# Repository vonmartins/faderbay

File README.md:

# FADERBAY

Current Status: Firmware not finnished.

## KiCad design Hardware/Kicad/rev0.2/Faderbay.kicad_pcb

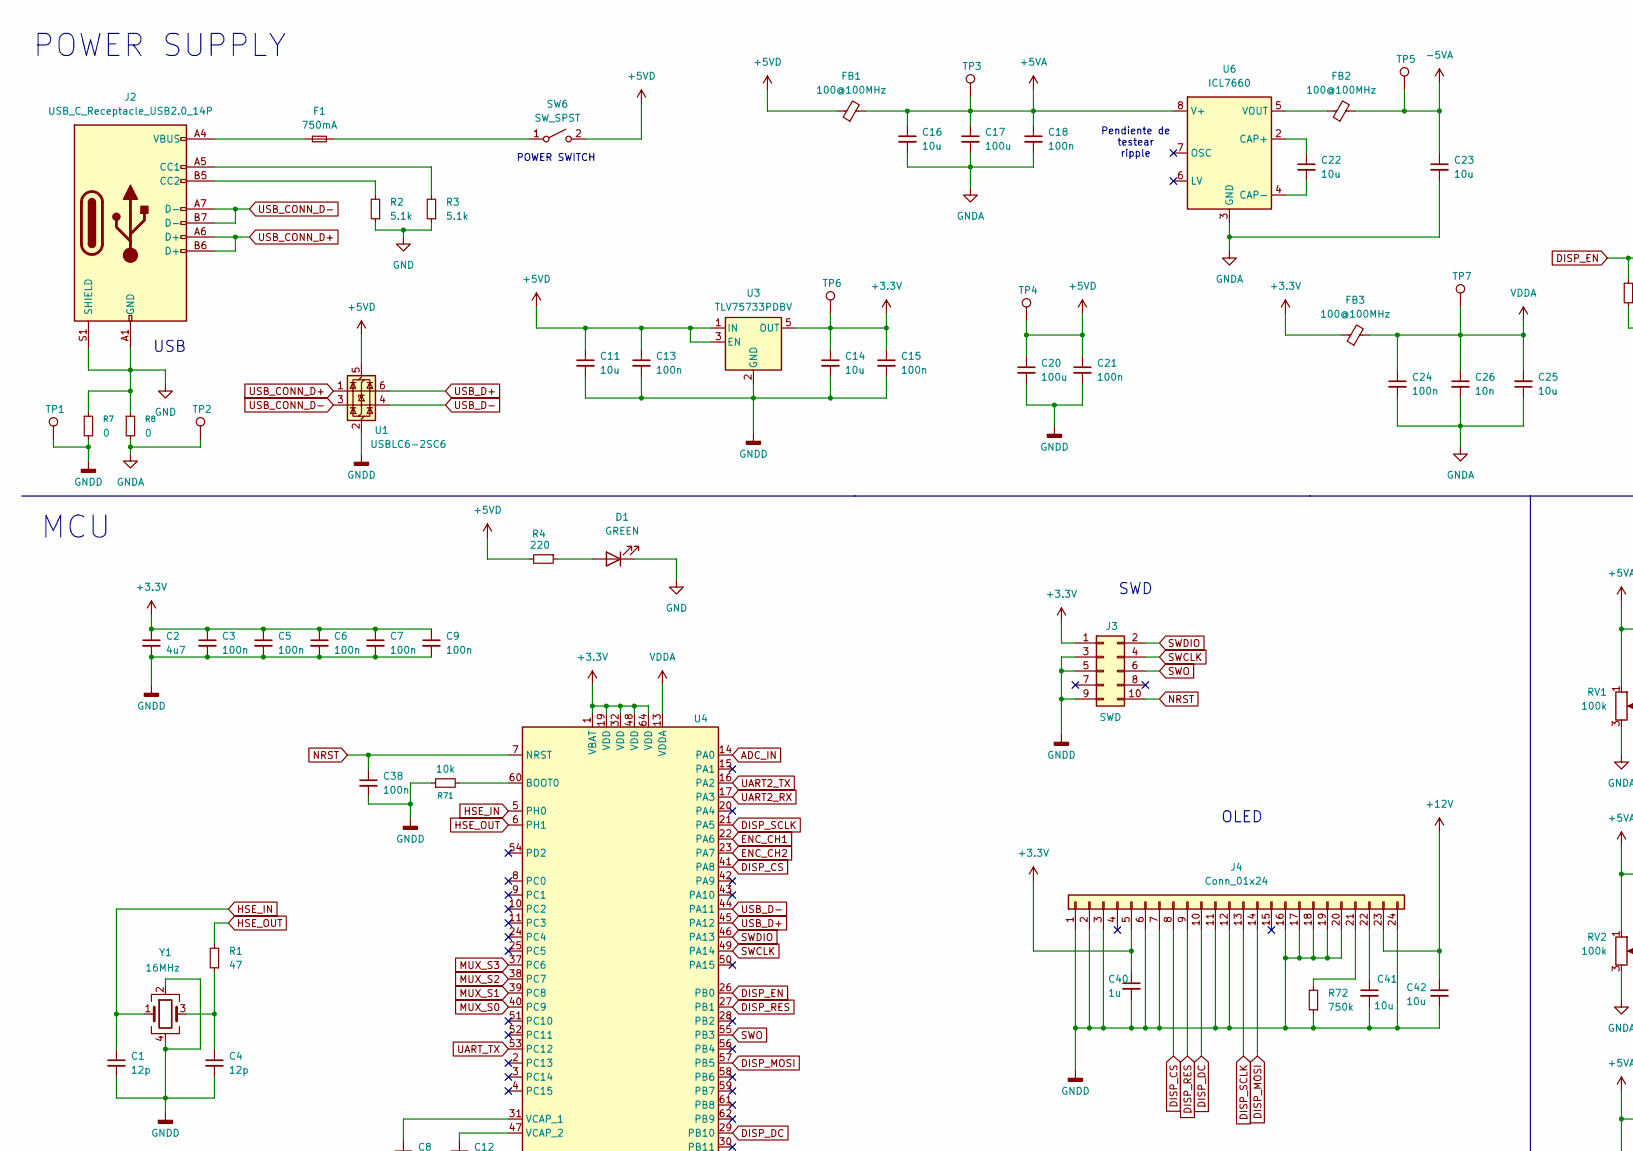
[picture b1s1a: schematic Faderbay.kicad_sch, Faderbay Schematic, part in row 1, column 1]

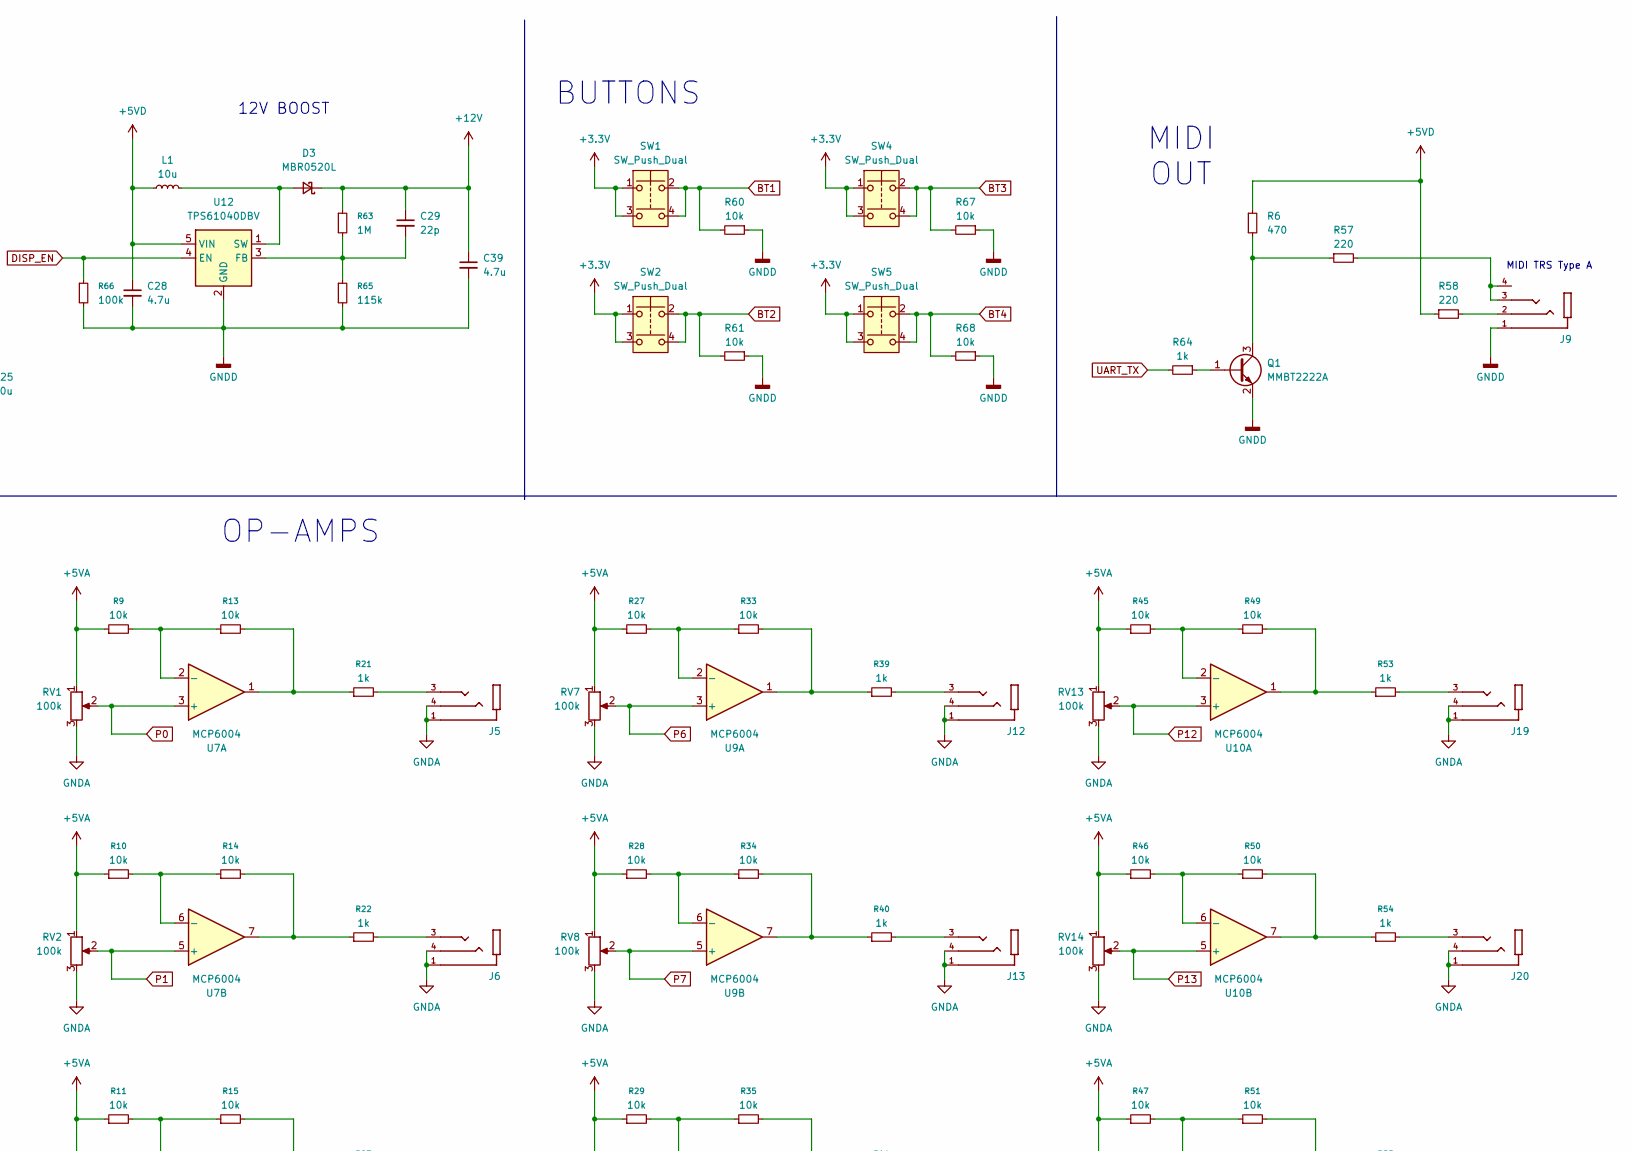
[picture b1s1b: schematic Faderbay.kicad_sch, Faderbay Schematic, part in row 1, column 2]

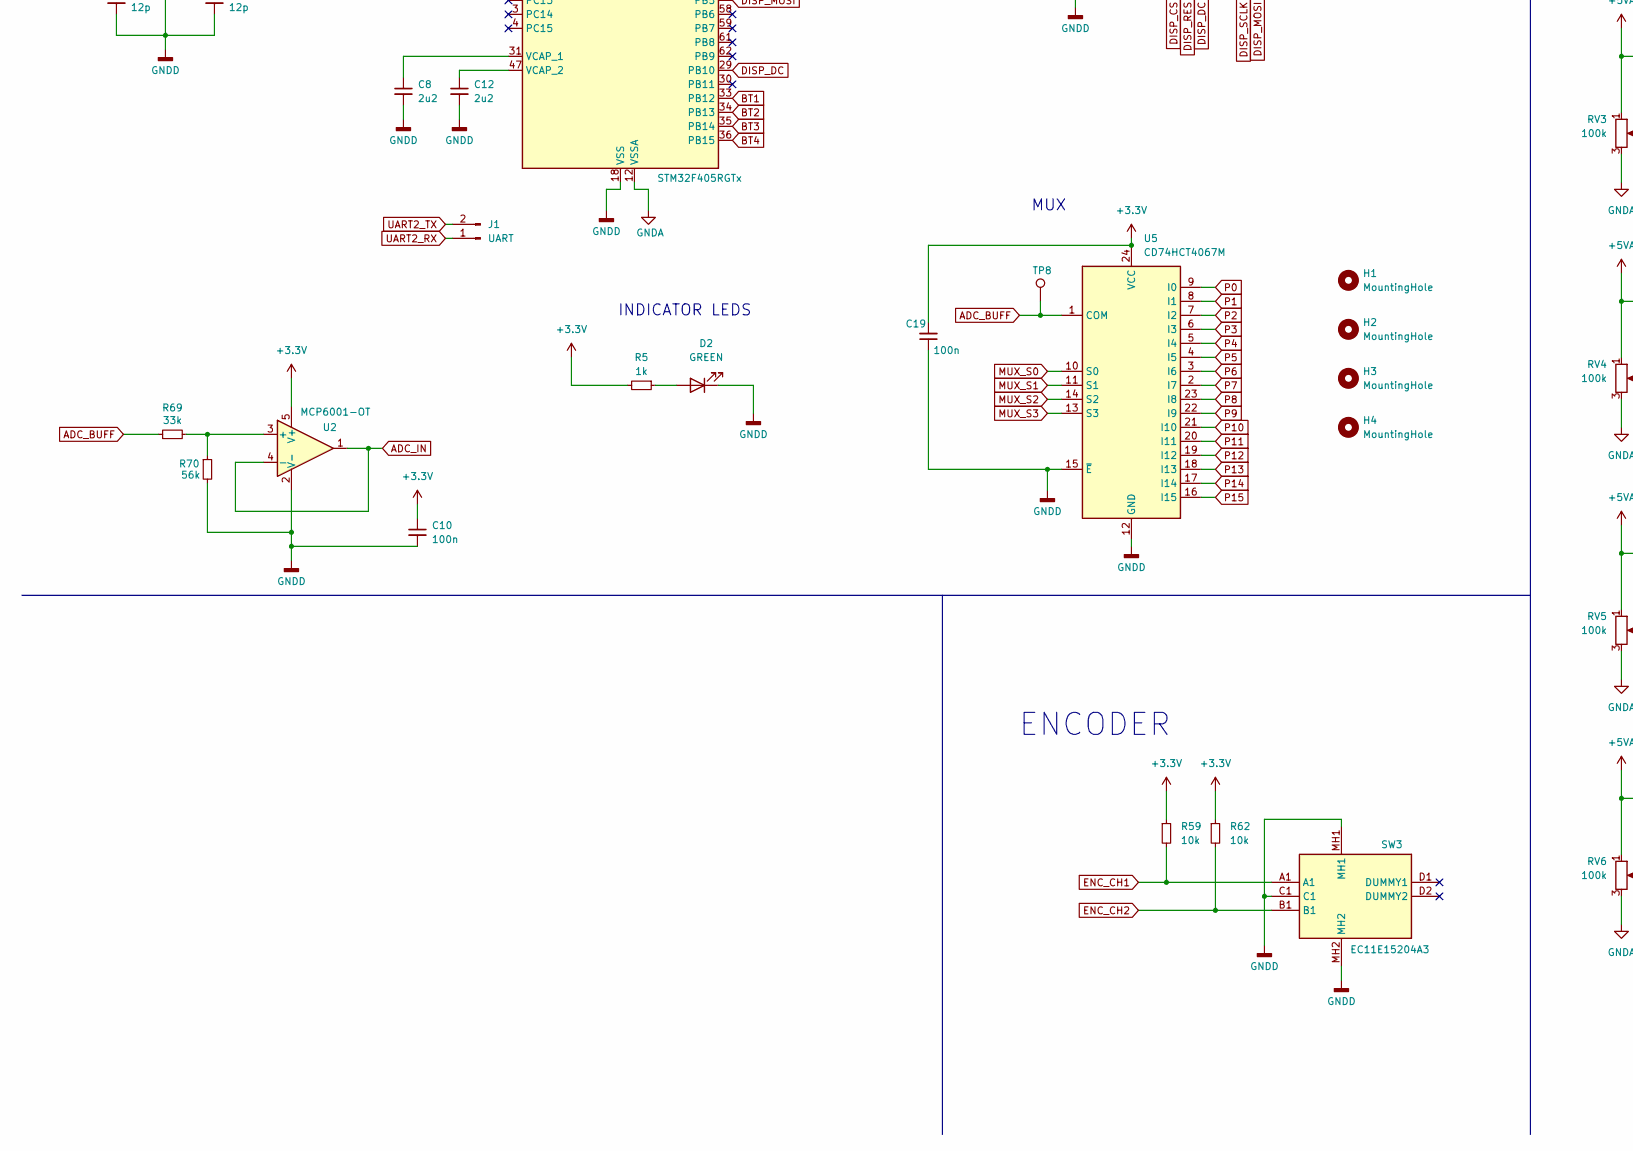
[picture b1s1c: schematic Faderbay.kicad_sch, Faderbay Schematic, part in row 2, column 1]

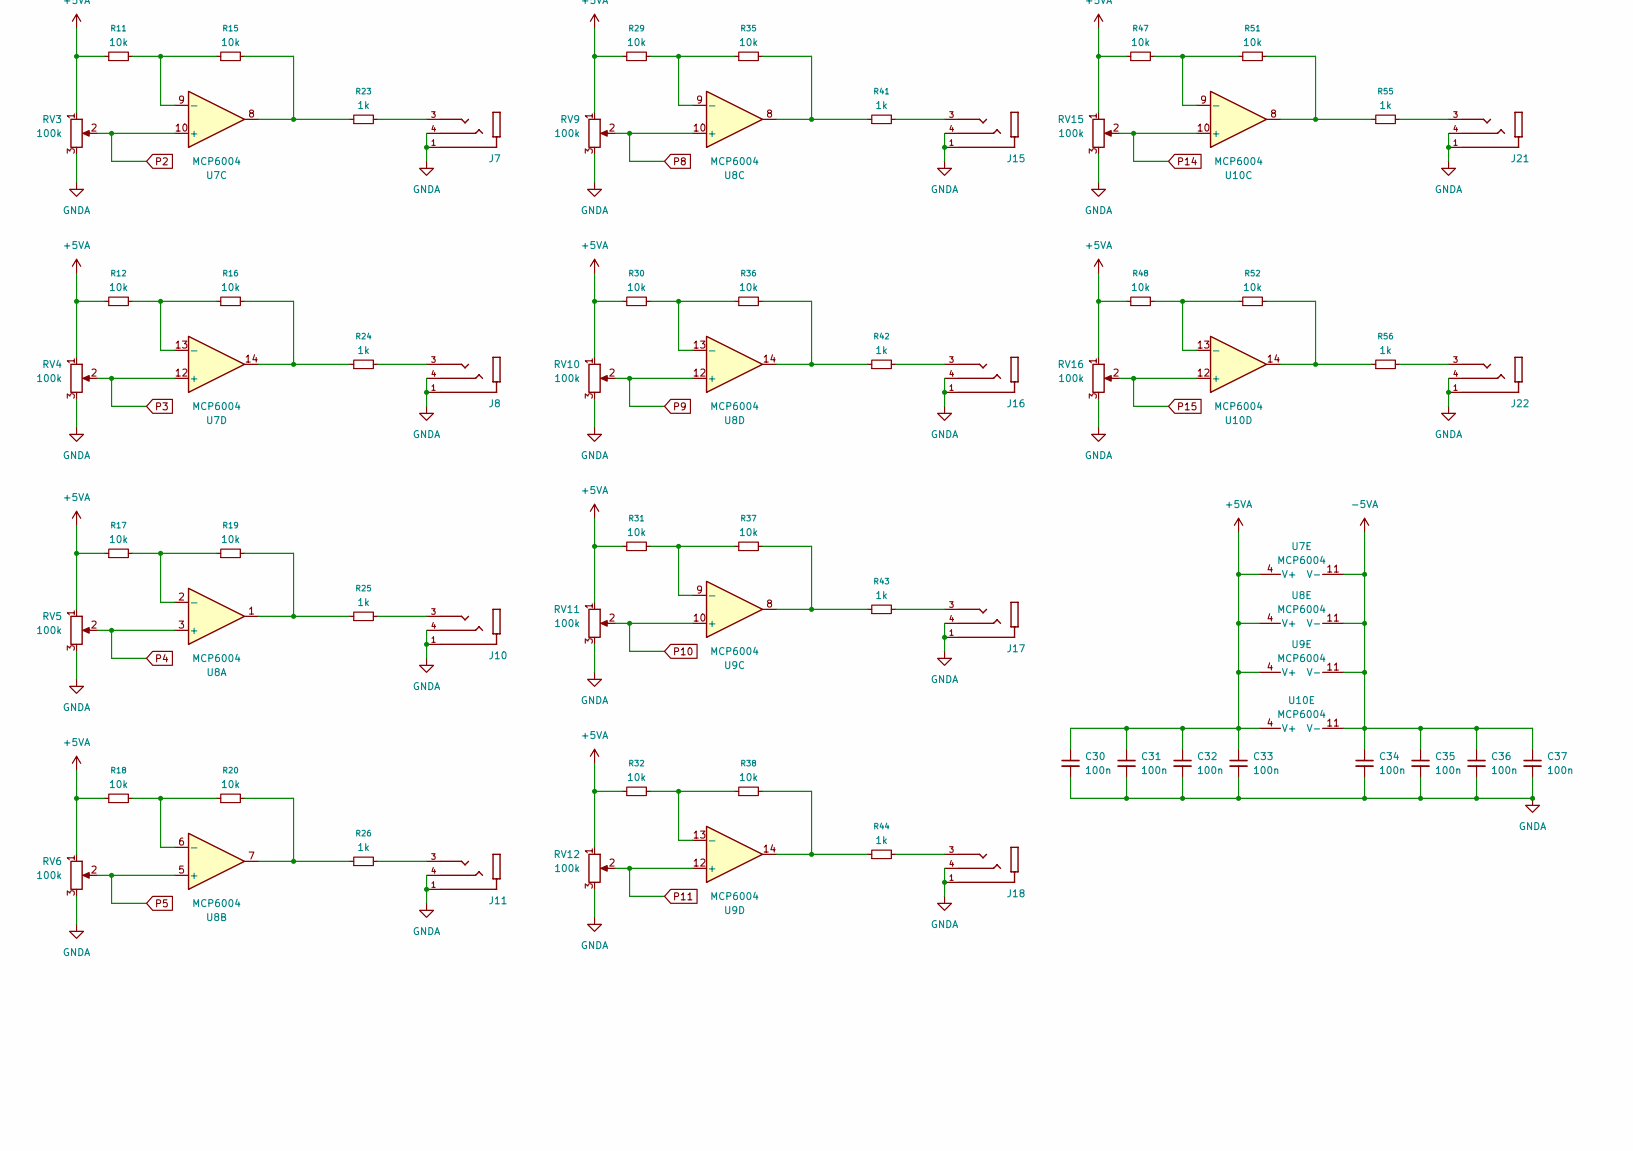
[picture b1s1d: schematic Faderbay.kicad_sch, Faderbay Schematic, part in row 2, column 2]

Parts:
C1, C4: 12p; C_0603_1608Metric; LCSC Part # C38523
C2: 4u7; C_0805_2012Metric; LCSC Part # C19666
C3, C5, C6, C7, C9, C13, C19: 100n; C_0402_1005Metric; LCSC Part # C1525
C8, C12: 2u2; C_0805_2012Metric; LCSC Part # C377773
C10, C15, C18, C30, C31, C32, C33, C34, C35, C36, C37, C38: 100n; C_0402_1005Metric
C11, C14, C16, C23: 10u; C_0805_2012Metric
C17: 100u; C_1206_3216Metric; LCSC Part # C12891
C20: 100u; C_1206_3216Metric
C21, C24: 100n; C_0402_1005Metric; LCSC Part # C52923
C22: 10u; C_1206_3216Metric
C25: 10u; C_0603_1608Metric; LCSC Part # C52923
C26: 10n; C_0402_1005Metric; LCSC Part # C52923
C28, C39: 4.7u; C_0805_2012Metric
C29: 22p; C_0402_1005Metric
C40: 1u; C_0603_1608Metric
C41, C42: 10u; C_0603_1608Metric
D1: GREEN; WP934EWGD
D2: GREEN; LED_0805_2012Metric; LCSC Part # C2297
D3: MBR0520L; D_0805_2012Metric
F1: 750mA; Fuse_1206_3216Metric
FB1, FB2, FB3: 100@100MHz; L_0805_2012Metric
H1, H2, H3, H4: MountingHole; MountingHole_3.2mm_M3
J1: UART; PinHeader_1x02_P2.54mm_Vertical
J2: USB_C_Receptacle_USB2.0_14P; USB_C_Receptacle_HRO_TYPE-C-31-M-12; LCSC Part # C5119948
J3: SWD; PinSocket_2x05_P1.27mm_Vertical_SMD; LCSC Part # C350283
J4: Conn_01x24; Jushuo_AFC07-S24FCA-00_1x24-1MP_P0.50_Horizontal
J5, J6, J7, J8, J10, J11, J12, J13, J15, J16, J17, J18, J19, J20, J21, J22: WQP729JH-R; LCSC Part # C18594
J9: WQP729JH-B; LCSC Part # C18594
L1: 10u; L_Sunlord_SWPA4030S
Q1: MMBT2222A; SOT-23; LCSC Part # C8512
R1: 47; R_0603_1608Metric; LCSC Part # C23182
R2, R3: 5.1k; R_0402_1005Metric; LCSC Part # C23186
R4: 220; R_0603_1608Metric; LCSC Part # C23193
R5: 1k; R_0603_1608Metric; LCSC Part # C17556
R6: 470; R_0603_1608Metric
R7: 0; R_0603_1608Metric; LCSC Part # C25803
R8: 0; R_0603_1608Metric; LCSC Part # C22793
R9, R10, R11, R12, R13, R14, R15, R16, R17, R18, R19, R20, R27, R28, R29, R30, R31, R32, R33, R34, R35, R36, R37, R38, R45, R46, R47, R48, R49, R50, R51, R52: 10k; R_0402_1005Metric
R21, R22, R39, R40, R53, R54: 1k; R_0603_1608Metric; LCSC Part # C4184
R23, R24, R25, R26, R41, R42, R43, R44, R55, R56: 1k; R_0603_1608Metric; LCSC Part # C21190
R57, R58: 220; R_0805_2012Metric; LCSC Part # C17556
R59, R60, R61, R62, R67, R68: 10k; R_0402_1005Metric; LCSC Part # C25531
R63: 1M; R_0402_1005Metric
R64: 1k; R_0402_1005Metric; LCSC Part # C25531
R65: 115k; R_0402_1005Metric
R66: 100k; R_0603_1608Metric
R69: 33k; R_0402_1005Metric
R70: 56k; R_0402_1005Metric
R71: 10k; C_0402_1005Metric
R72: 750k; R_0603_1608Metric
RV1, RV2, RV3, RV4, RV5, RV6, RV7, RV8, RV9, RV10, RV11, RV12, RV13, RV14, RV15, RV16: 100k; Potentiometer_Bourns_PTA6043_Single_Slide
SW1, SW2, SW4, SW5: SW_Push_Dual; 430182070816; LCSC Part # C318884
SW3: EC11E15204A3; Mouser Part Number 688-EC11E15204A3
SW6: SW_SPST; RA1H1C112R
TP1, TP2, TP3, TP4, TP5, TP6, TP7, TP8: TestPoint; TestPoint_Loop_D2.50mm_Drill1.0mm
U1: USBLC6-2SC6; SOT-23-6; LCSC Part # C7519
U2: MCP6001-OT; SOT-23-5
U3: TLV75733PDBV; SOT-23-5
U4: STM32F405RGTx; LQFP-64_10x10mm_P0.5mm; LCSC Part # C15742
U5: CD74HCT4067M; SOIC-24W_7.5x15.4mm_P1.27mm; LCSC Part # C496123
U6: ICL7660; SOIC-8_3.9x4.9mm_P1.27mm
U7, U8, U9, U10: MCP6004; TSSOP-14_4.4x5mm_P0.65mm
U12: TPS61040DBV; SOT-23-5
Y1: 16MHz; Crystal_SMD_3225-4Pin_3.2x2.5mm; LCSC Part # C13738

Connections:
+3.3V: C2.1, C3.1, C5.1, C6.1, C7.1, C9.1, C10.1, C14.1, C15.1, C19.2, C40.1, FB3.1, J3.1, J4.5, R5.2, R59.1, R62.1, SW1.1, SW1.3, SW2.1, SW2.3, SW4.1, SW4.3, SW5.1, SW5.3, TP6.1 (1_1), U2.5 (V+), U3.5 (OUT), U4.1 (VBAT), U4.19 (VDD), U4.32 (VDD), U4.48 (VDD), U4.64 (VDD), U5.24 (VCC)
+5VA: C16.1, C17.1, C18.1, C30.1, C31.1, C32.1, C33.1, FB1.2, R9.1, R10.1, R11.1, R12.1, R17.1, R18.1, R27.1, R28.1, R29.1, R30.1, R31.1, R32.1, R45.1, R46.1, R47.1, R48.1, RV1.1, RV2.1, RV3.1, RV4.1, RV5.1, RV6.1, RV7.1, RV8.1, RV9.1, RV10.1, RV11.1, RV12.1, RV13.1, RV14.1, RV15.1, RV16.1, TP3.1 (1_1), U6.8 (V+), U7.4 (V+), U8.4 (V+), U9.4 (V+), U10.4 (V+)
+12V: C29.1, C39.1, C42.1, D3.1 (K), J4.23, R63.1
-5VA: C23.1, C34.1, C35.1, C36.1, C37.1, FB2.2, TP5.1 (1_1), U7.11 (V-), U8.11 (V-), U9.11 (V-), U10.11 (V-)
ADC_BUFF: R69.1, TP8.1 (1_1), U5.1 (COM)
ADC_IN: U2.1, U2.4 (-), U4.14 (PA0)
BT1: R60.2, SW1.2, SW1.4, U4.33 (PB12)
BT2: R61.2, SW2.2, SW2.4, U4.34 (PB13)
BT3: R67.2, SW4.2, SW4.4, U4.35 (PB14)
BT4: R68.2, SW5.2, SW5.4, U4.36 (PB15)
DISP_CS: J4.8, U4.41 (PA8)
DISP_DC: J4.10, U4.29 (PB10)
DISP_EN: R66.1, U4.26 (PB0), U12.4 (EN)
DISP_MOSI: J4.14, U4.57 (PB5)
DISP_RES: J4.9, U4.27 (PB1)
DISP_SCLK: J4.13, U4.21 (PA5)
ENC_CH1: R59.2, SW3.A1, U4.22 (PA6)
ENC_CH2: R62.2, SW3.B1, U4.23 (PA7)
GND: D1.1 (K), J2.A1 (GND), J2.A12 (GND), J2.B1 (GND), J2.B12 (GND), J2.S1 (SHIELD), R2.1, R3.1, R7.1, R8.1
GNDA: C16.2, C17.2, C18.2, C23.2, C24.2, C25.1, C26.2, C30.2, C31.2, C32.2, C33.2, C34.2, C35.2, C36.2, C37.2, J5.1, J5.4, J6.1, J6.4, J7.1, J7.4, J8.1, J8.4, J10.1, J10.4, J11.1, J11.4, J12.1, J12.4, J13.1, J13.4, J15.1, J15.4, J16.1, J16.4, J17.1, J17.4, J18.1, J18.4, J19.1, J19.4, J20.1, J20.4, J21.1, J21.4, J22.1, J22.4, R8.2, RV1.3, RV2.3, RV3.3, RV4.3, RV5.3, RV6.3, RV7.3, RV8.3, RV9.3, RV10.3, RV11.3, RV12.3, RV13.3, RV14.3, RV15.3, RV16.3, TP2.1 (1_1), U4.12 (VSSA), U6.3 (GND)
HSE_IN: C1.1, U4.5 (PH0), Y1.1
HSE_OUT: R1.2, U4.6 (PH1)
MUX_S0: U4.40 (PC9), U5.10 (S0)
MUX_S1: U4.39 (PC8), U5.11 (S1)
MUX_S2: U4.38 (PC7), U5.14 (S2)
MUX_S3: U4.37 (PC6), U5.13 (S3)
NRST: C38.1, J3.10, U4.7 (NRST)
unnamed: C4.1, R1.1, Y1.3
unnamed: D1.2 (A), R4.1
unnamed: D2.2 (A), R5.1
unnamed: D3.2 (A), L1.2, U12.1 (SW)
unnamed: F1.1, J2.A4 (VBUS), J2.A9 (VBUS), J2.B4 (VBUS), J2.B9 (VBUS)
unnamed: J2.A5 (CC1), R3.2
unnamed: J2.B5 (CC2), R2.2
unnamed: J4.21, R72.2
unnamed: C41.1, J4.22
unnamed: J5.3, R21.2
unnamed: J6.3, R22.2
unnamed: J7.3, R23.2
unnamed: J8.3, R24.2
unnamed: J9.2, R58.2
unnamed: J9.3, J9.4, R57.2
unnamed: J10.3, R25.2
unnamed: J11.3, R26.2
unnamed: J12.3, R39.2
unnamed: J13.3, R40.2
unnamed: J15.3, R41.2
unnamed: J16.3, R42.2
unnamed: J17.3, R43.2
unnamed: J18.3, R44.2
unnamed: J19.3, R53.2
unnamed: J20.3, R54.2
unnamed: J21.3, R55.2
unnamed: J22.3, R56.2
unnamed: Q1.1 (B), R64.1
unnamed: Q1.3 (C), R6.2, R57.1
unnamed: R13.2, R21.1, U7.1
unnamed: R14.2, R22.1, U7.7
unnamed: R15.2, R23.1, U7.8
unnamed: R16.2, R24.1, U7.14
unnamed: R19.2, R25.1, U8.1
unnamed: R20.2, R26.1, U8.7
unnamed: R33.2, R39.1, U9.1
unnamed: R34.2, R40.1, U9.7
unnamed: R35.2, R41.1, U8.8
unnamed: R36.2, R42.1, U8.14
unnamed: R37.2, R43.1, U9.8
unnamed: R38.2, R44.1, U9.14
unnamed: R49.2, R53.1, U10.1
unnamed: R50.2, R54.1, U10.7
unnamed: R51.2, R55.1, U10.8
unnamed: R52.2, R56.1, U10.14
unnamed: F1.2, SW6.1 (A)
unnamed: R69.2, R70.1, U2.3 (+)
unnamed: R71.2, U4.60 (BOOT0)
unnamed: C8.1, U4.31 (VCAP_1)
unnamed: C12.1, U4.47 (VCAP_2)
unnamed: C22.1, U6.2 (CAP+)
unnamed: C22.2, U6.4 (CAP-)
unnamed: FB2.1, U6.5 (VOUT)
unnamed: R9.2, R13.1, U7.2 (-)
unnamed: R10.2, R14.1, U7.6 (-)
unnamed: R11.2, R15.1, U7.9 (-)
unnamed: R12.2, R16.1, U7.13 (-)
unnamed: R17.2, R19.1, U8.2 (-)
unnamed: R18.2, R20.1, U8.6 (-)
unnamed: R29.2, R35.1, U8.9 (-)
unnamed: R30.2, R36.1, U8.13 (-)
unnamed: R27.2, R33.1, U9.2 (-)
unnamed: R28.2, R34.1, U9.6 (-)
unnamed: R31.2, R37.1, U9.9 (-)
unnamed: R32.2, R38.1, U9.13 (-)
unnamed: R45.2, R49.1, U10.2 (-)
unnamed: R46.2, R50.1, U10.6 (-)
unnamed: R47.2, R51.1, U10.9 (-)
unnamed: R48.2, R52.1, U10.13 (-)
P0: RV1.2, U5.9 (I0), U7.3 (+)
P1: RV2.2, U5.8 (I1), U7.5 (+)
P2: RV3.2, U5.7 (I2), U7.10 (+)
P3: RV4.2, U5.6 (I3), U7.12 (+)
P4: RV5.2, U5.5 (I4), U8.3 (+)
P5: RV6.2, U5.4 (I5), U8.5 (+)
P6: RV7.2, U5.3 (I6), U9.3 (+)
P7: RV8.2, U5.2 (I7), U9.5 (+)
P8: RV9.2, U5.23 (I8), U8.10 (+)
P9: RV10.2, U5.22 (I9), U8.12 (+)
P10: RV11.2, U5.21 (I10), U9.10 (+)
P11: RV12.2, U5.20 (I11), U9.12 (+)
P12: RV13.2, U5.19 (I12), U10.3 (+)
P13: RV14.2, U5.18 (I13), U10.5 (+)
P14: RV15.2, U5.17 (I14), U10.10 (+)
P15: RV16.2, U5.16 (I15), U10.12 (+)
SWCLK: J3.4, U4.49 (PA14)
SWDIO: J3.2, U4.46 (PA13)
SWO: J3.6, U4.55 (PB3)
UART2_RX: J1.1, U4.17 (PA3)
UART2_TX: J1.2, U4.16 (PA2)
UART_TX: R64.2, U4.53 (PC12)
USB_CONN_D+: J2.A6 (D+), J2.B6 (D+), U1.1 (I/O1)
USB_CONN_D-: J2.A7 (D-), J2.B7 (D-), U1.3 (I/O2)
USB_D+: U1.6 (I/O1), U4.45 (PA12)
USB_D-: U1.4 (I/O2), U4.44 (PA11)
VDDA: C24.1, C25.2, C26.1, FB3.2, TP7.1 (1_1), U4.13 (VDDA)

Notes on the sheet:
Pendiente de testear ripple
12V BOOST
BUTTONS
MIDI OUT
MCU
USB
MUX
MIDI TRS Type A
POWER SWITCH
INDICATOR LEDS
POWER SUPPLY
SWD
OLED
ENCODER
OP-AMPS

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
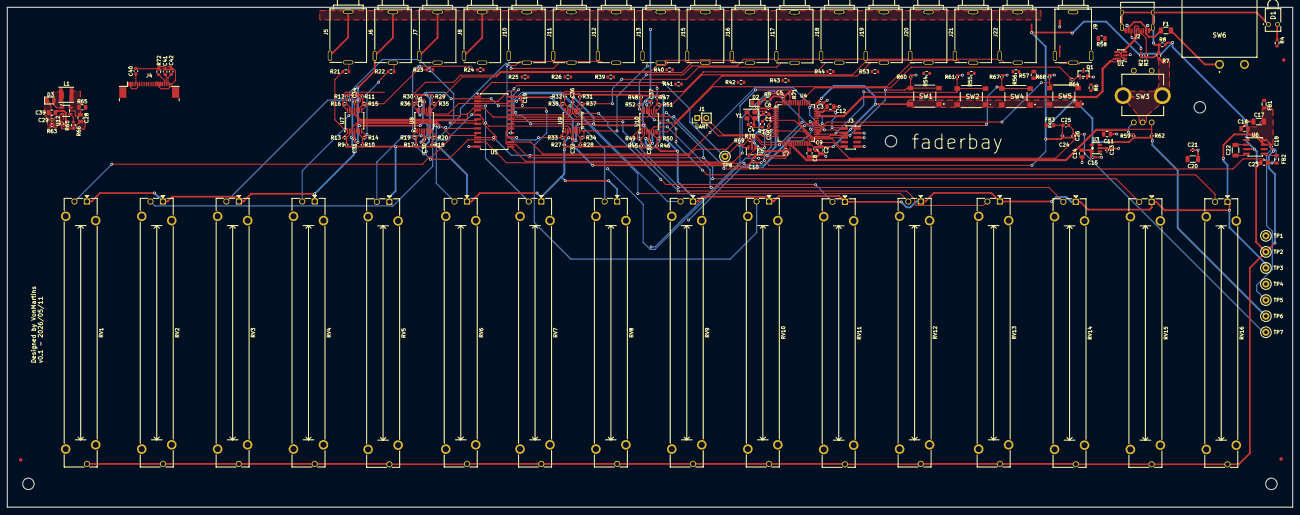
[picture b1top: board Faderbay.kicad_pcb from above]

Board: 4 copper layers, 360.0 x 140.0 mm, 193 parts (0 on the bottom side), 126 nets.

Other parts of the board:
FID1, FID2, FID3: Fiducial_1mm_Mask2mm
R65#2: 115k; R_0402_1005Metric

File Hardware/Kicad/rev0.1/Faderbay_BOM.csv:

"Value","Reference","Footprint","LCSC Part #"
"12p","C1","Capacitor_SMD:C_0603_1608Metric","C38523"
"4u7","C2","Capacitor_SMD:C_0603_1608Metric","C19666"
"100n","C3","Capacitor_SMD:C_0402_1005Metric","C1525"
"12p","C4","Capacitor_SMD:C_0603_1608Metric","C38523"
"100n","C5","Capacitor_SMD:C_0402_1005Metric","C1525"
"100n","C6","Capacitor_SMD:C_0402_1005Metric","C1525"
"100n","C7","Capacitor_SMD:C_0402_1005Metric","C1525"
"2u2","C8","Capacitor_SMD:C_0805_2012Metric","C377773"
"100n","C9","Capacitor_SMD:C_0402_1005Metric","C1525"
"100n","C10","Capacitor_SMD:C_0402_1005Metric",""
"10u","C11","",""
"2u2","C12","Capacitor_SMD:C_0805_2012Metric","C377773"
"100n","C13","Capacitor_SMD:C_0402_1005Metric",""
"10u","C14","Capacitor_SMD:C_0402_1005Metric",""
"100n","C15","Capacitor_SMD:C_0402_1005Metric",""
"10u","C16","",""
"100u","C17","",""
"100n","C18","Capacitor_SMD:C_0402_1005Metric",""
"100n","C19","Capacitor_SMD:C_0402_1005Metric","C1525"
"100u","C20","",""
"100n","C21","",""
"10u","C22","",""
"10u","C23","",""
"100n","C24","Capacitor_SMD:C_0402_1005Metric","C52923"
"10u","C25","Capacitor_SMD:C_0402_1005Metric","C52923"
"10n","C26","Capacitor_SMD:C_0402_1005Metric","C52923"
"4,7u","C27","Capacitor_SMD:C_0402_1005Metric","C23733"
"100n","C28","Capacitor_SMD:C_0402_1005Metric","C1525"
"100n","C29","Capacitor_SMD:C_0402_1005Metric","C1525"
"100n","C30","",""
"100n","C31","",""
"100n","C32","",""
"100n","C33","",""
"100n","C34","",""
"100n","C35","",""
"100n","C36","",""
"100n","C37","",""
"GREEN","D1","User:WP934EWGD",""
"GREEN","D2","LED_SMD:LED_0805_2012Metric","C2297"
"WHITE","D3","LED_SMD:LED_0603_1608Metric"," C2290"
"750mA","F1","Fuse:Fuse_1206_3216Metric",""
"100@100MHz","FB1","Inductor_SMD:L_0805_2012Metric",""
"100@100MHz","FB2","Inductor_SMD:L_0805_2012Metric",""
"100@100MHz","FB3","Inductor_SMD:L_0805_2012Metric",""
"UART","J1","",""
"USB_C_Receptacle_USB2.0_14P","J2","User:USB_C_Receptacle_Amphenol_12401610E4-2A","C5119948"
"SWD","J3","Connector_PinSocket_1.27mm:PinSocket_2x05_P1.27mm_Vertical_SMD","C350283"
"52437-2471","J4","User:524372471","C3169564"
"~","J5","User:PJ-320B","C18594"
"~","J6","User:PJ-320B","C18594"
"~","J7","User:PJ-320B","C18594"
"~","J8","User:PJ-320B","C18594"
"~","J9","User:PJ-320B","C18594"
"~","J10","User:PJ-320B","C18594"
"~","J11","User:PJ-320B","C18594"
"~","J12","User:PJ-320B","C18594"
"~","J13","User:PJ-320B","C18594"
"MIDI DIN-5","J14","User:MIDI_DIN5",""
"~","J15","User:PJ-320B","C18594"
"~","J16","User:PJ-320B","C18594"
"~","J17","User:PJ-320B","C18594"
"~","J18","User:PJ-320B","C18594"
"~","J19","User:PJ-320B","C18594"
"~","J20","User:PJ-320B","C18594"
"~","J21","User:PJ-320B","C18594"
"~","J22","User:PJ-320B","C18594"
"MMBT2222A","Q2","Package_TO_SOT_SMD:SOT-23","C8512"
"47","R1","Resistor_SMD:R_0603_1608Metric","C23182"
"5.1k","R2","Resistor_SMD:R_0402_1005Metric","C23186"
"5.1k","R3","Resistor_SMD:R_0402_1005Metric","C23186"
"230","R4","Resistor_SMD:R_0603_1608Metric","C23193"
"220","R5","Resistor_SMD:R_0603_1608Metric","C17556"
"220","R6","Resistor_SMD:R_0603_1608Metric","C17556"
"0","R7","Resistor_SMD:R_0603_1608Metric",""
"0","R8","Resistor_SMD:R_0603_1608Metric",""
"10k","R9","Fuse:Fuse_1206_3216Metric",""
"10k","R10","",""
"10k","R11","",""
"10k","R12","",""
"10k","R13","",""
"10k","R14","",""
"10k","R15","",""
"10k","R16","",""
"10k","R17","",""
"10k","R18","",""
"10k","R19","",""
"10k","R20","",""
"1k","R21","Resistor_SMD:R_0603_1608Metric",""
"1k","R22","Resistor_SMD:R_0603_1608Metric",""
"1k","R23","Resistor_SMD:R_0603_1608Metric",""
"1k","R24","Resistor_SMD:R_0603_1608Metric",""
"1k","R25","Resistor_SMD:R_0603_1608Metric",""
"1k","R26","Resistor_SMD:R_0603_1608Metric",""
"10k","R27","",""
"10k","R28","",""
"10k","R29","",""
"10k","R30","",""
"10k","R31","",""
"10k","R32","Resistor_SMD:R_0402_1005Metric",""
"10k","R33","Resistor_SMD:R_0402_1005Metric",""
"10k","R34","Resistor_SMD:R_0402_1005Metric",""
"10k","R35","Resistor_SMD:R_0402_1005Metric",""
"10k","R36","Resistor_SMD:R_0402_1005Metric",""
"10k","R37","Resistor_SMD:R_0402_1005Metric",""
"10k","R38","Resistor_SMD:R_0402_1005Metric",""
"1k","R39","Resistor_SMD:R_0603_1608Metric",""
"1k","R40","Resistor_SMD:R_0603_1608Metric",""
"1k","R41","Resistor_SMD:R_0603_1608Metric",""
"1k","R42","Resistor_SMD:R_0603_1608Metric",""
"1k","R43","Resistor_SMD:R_0603_1608Metric",""
"1k","R44","Resistor_SMD:R_0603_1608Metric",""
"10k","R45","Resistor_SMD:R_0402_1005Metric",""
"10k","R46","Resistor_SMD:R_0402_1005Metric",""
"10k","R47","Resistor_SMD:R_0402_1005Metric",""
"10k","R48","Resistor_SMD:R_0402_1005Metric",""
"10k","R49","Resistor_SMD:R_0402_1005Metric",""
"10k","R50","Resistor_SMD:R_0402_1005Metric",""
"10k","R51","Resistor_SMD:R_0402_1005Metric",""
"10k","R52","Resistor_SMD:R_0402_1005Metric",""
"1k","R53","Resistor_SMD:R_0402_1005Metric",""
"1k","R54","Resistor_SMD:R_0402_1005Metric",""
"1k","R55","Resistor_SMD:R_0402_1005Metric",""
"1k","R56","Resistor_SMD:R_0402_1005Metric",""
"220","R57","Resistor_SMD:R_0805_2012Metric","C17556"
"220","R58","Resistor_SMD:R_0805_2012Metric","C17556"
"10k","R59","Resistor_SMD:R_0402_1005Metric","C25531"
"10k","R60","Resistor_SMD:R_0402_1005Metric","C25531"
"10k","R61","Resistor_SMD:R_0402_1005Metric","C25531"
"10k","R62","Resistor_SMD:R_0402_1005Metric","C25531"
"220","R63","Resistor_SMD:R_0805_2012Metric","C17556"
"1k","R64","Resistor_SMD:R_0402_1005Metric","C25531"
"220","R66","Resistor_SMD:R_0805_2012Metric","C17556"
"10k","R67","Resistor_SMD:R_0402_1005Metric","C25531"
"10k","R68","Resistor_SMD:R_0402_1005Metric","C25531"
"910k","R69","Resistor_SMD:R_0603_1608Metric","C25800"
"100k","RV1","User:PTB60442010BPA104",""
"100k","RV2","User:PTB60442010BPA104",""
"100k","RV3","User:PTB60442010BPA104",""
"100k","RV4","User:PTB60442010BPA104",""
"100k","RV5","User:PTB60442010BPA104",""
"100k","RV6","User:PTB60442010BPA104",""
"100k","RV7","User:PTB60442010BPA104",""
"100k","RV8","User:PTB60442010BPA104",""
"100k","RV9","User:PTB60442010BPA104",""
"100k","RV10","User:PTB60442010BPA104",""
"100k","RV11","User:PTB60442010BPA104",""
"100k","RV12","User:PTB60442010BPA104",""
"100k","RV13","User:PTB60442010BPA104",""
"100k","RV14","User:PTB60442010BPA104",""
"100k","RV15","User:PTB60442010BPA104",""
"100k","RV16","User:PTB60442010BPA104",""
"LC2255EENPTAGBLK","S1","User:LC2255EENPTAGBLK",""
"SW_Push_Dual","SW1","Button_Switch_SMD:SW_Push_1P1T_XKB_TS-1187A","C318884"
"SW_Push_Dual","SW2","Button_Switch_SMD:SW_Push_1P1T_XKB_TS-1187A","C318884"
"EC11E15204A3","SW3","User:EC11E15204A3",""
"SW_Push_Dual","SW4","Button_Switch_SMD:SW_Push_1P1T_XKB_TS-1187A","C318884"
"SW_Push_Dual","SW5","Button_Switch_SMD:SW_Push_1P1T_XKB_TS-1187A","C318884"
"TestPoint","TP1","Resistor_SMD:R_0603_1608Metric",""
"TestPoint","TP2","Resistor_SMD:R_0805_2012Metric",""
"TestPoint","TP3","Resistor_SMD:R_0805_2012Metric",""
"TestPoint","TP4","Resistor_SMD:R_0603_1608Metric",""
"TestPoint","TP5","",""
"TestPoint","TP6","",""
"TestPoint","TP7","",""
"TestPoint","TP8","",""
"USBLC6-2SC6","U1","Package_TO_SOT_SMD:SOT-23-6","C7519"
"MCP6001-OT","U2","Package_TO_SOT_SMD:SOT-23-5",""
"TLV75733PDBV","U3","Package_TO_SOT_SMD:SOT-23-5",""
"STM32F405RGTx","U4","Package_QFP:LQFP-64_10x10mm_P0.5mm","C15742"
"CD74HC4067M","U5","Package_SO:SOIC-24W_7.5x15.4mm_P1.27mm","C496123"
"ICL7660","U6","Package_SO:SOIC-8_3.9x4.9mm_P1.27mm",""
"MCP6004","U7","Package_SO:TSSOP-14_4.4x5mm_P0.65mm",""
"MCP6004","U8","Package_SO:TSSOP-14_4.4x5mm_P0.65mm",""
"MCP6004","U9","Package_SO:TSSOP-14_4.4x5mm_P0.65mm",""
"MCP6004","U10","Package_SO:TSSOP-14_4.4x5mm_P0.65mm",""
"16MHz","Y1","Crystal:Crystal_SMD_3225-4Pin_3.2x2.5mm","C13738"

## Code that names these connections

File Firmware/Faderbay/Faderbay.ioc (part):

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Mcu.Name=STM32F405RGTx
Mcu.Package=LQFP64
Mcu.UserName=STM32F405RGTx
PA0-WKUP.Signal=ADCx_IN0
PA11.Mode=Device_Only
PA11.Signal=USB_OTG_FS_DM
PA12.Mode=Device_Only
PA12.Signal=USB_OTG_FS_DP
PA13.Mode=Trace_Asynchronous_SW
PA13.Signal=SYS_JTMS-SWDIO
PA14.Mode=Trace_Asynchronous_SW
PA14.Signal=SYS_JTCK-SWCLK
PA2.Mode=Asynchronous
PA2.Signal=USART2_TX
PA3.Mode=Asynchronous
PA3.Signal=USART2_RX
PA5.Mode=TX_Only_Simplex_Unidirect_Master
PA5.Signal=SPI1_SCK
PA6.Signal=S_TIM3_CH1
PA7.Signal=S_TIM3_CH2
PA8.GPIOParameters=GPIO_Label
PA8.GPIO_Label=DISP_CS
PA8.Signal=GPIO_Output
PA9.Mode=Activate_VBUS
PA9.Signal=USB_OTG_FS_VBUS
PB12.GPIOParameters=GPIO_PuPd,GPIO_Label
PB12.GPIO_Label=BTN_1
PB12.GPIO_PuPd=GPIO_NOPULL
PB12.Signal=GPIO_Input
PB13.GPIOParameters=GPIO_PuPd,GPIO_Label
PB13.GPIO_Label=BTN_2
PB13.GPIO_PuPd=GPIO_NOPULL
PB13.Signal=GPIO_Input
PB14.GPIOParameters=GPIO_PuPd,GPIO_Label
PB14.GPIO_Label=BTN_3
PB14.GPIO_PuPd=GPIO_NOPULL
PB14.Signal=GPIO_Input
PB15.GPIOParameters=GPIO_PuPd,GPIO_Label
PB15.GPIO_Label=BTN_4
PB15.GPIO_PuPd=GPIO_NOPULL
PB15.Signal=GPIO_Input
PB3.Mode=Trace_Asynchronous_SW
PB3.Signal=SYS_JTDO-SWO
PB5.Mode=TX_Only_Simplex_Unidirect_Master
PB5.Signal=SPI1_MOSI
PC12.Mode=Asynchronous
PC12.Signal=UART5_TX
PC6.GPIOParameters=GPIO_Label
PC6.GPIO_Label=MUX_S3
PC6.Signal=GPIO_Output
PC7.GPIOParameters=GPIO_Label
PC7.GPIO_Label=MUX_S2
PC7.Signal=GPIO_Output
PC8.GPIOParameters=GPIO_Label
PC8.GPIO_Label=MUX_S1
PC8.Signal=GPIO_Output
PC9.GPIOParameters=GPIO_Label
PC9.GPIO_Label=MUX_S0
PC9.Signal=GPIO_Output
PD2.Mode=Asynchronous
PD2.Signal=UART5_RX
PH0-OSC_IN.Mode=HSE-External-Oscillator
PH0-OSC_IN.Signal=RCC_OSC_IN
PH1-OSC_OUT.Mode=HSE-External-Oscillator
PH1-OSC_OUT.Signal=RCC_OSC_OUT
RCC.HSE_VALUE=12000000
RCC.SYSCLKFreq_VALUE=72000000
RCC.SYSCLKSource=RCC_SYSCLKSOURCE_PLLCLK
board=custom

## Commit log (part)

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2025-02-12 12/02
2025-02-12 Creating files
2025-02-13 Coding UI Interfaces
2025-03-02 Implementing CLI
2025-03-02 Add project structure documentation and initial README for Faderbay
2025-03-02 Deleted Local Files
2025-03-08 Track Config Files
2025-03-08 Updating .gitignore
2025-03-08 updating .gitignoring
2025-03-08 Flash API Added
2025-03-08 Refactor UI and device structures; add configuration handling and initialization logic
2025-03-08 Documentation Added
2025-03-08 CLI Functions Updated
2025-03-08 Add new CLI functions for default configuration and preset erasure
2025-03-08 Add MIDI header and source files
2025-03-08 Add MIDI source file to CMake build configuration
2025-03-08 Fix header guard naming convention in button.h
2025-03-08 Add UI mode and editing functionality to device management
2025-03-08 Rename button defines for improved clarity and functionality
2025-03-08 Add NUM_CONFIGS definition to config.h for configuration management
2025-03-10 Add USART2 for CLI
2025-03-10 Add USART2 in .ioc
2025-03-10 Add Init_Presets function to initialize device presets
2025-03-10 Add USART2 support and update CLI command handling
2025-03-13 Add MIDI Device Config
2025-03-14 Add MIDI message structure and sendMidiCC
2025-03-14 Add USB device support with initialization and request handling
2025-03-15 Remove USB device implementation
2025-03-15 Remove USART1 and USB OTG FS support from HAL configuration and interrupt handlers
2025-03-15 Refactor CMakeLists.txt to remove USB device support and add ADC source files
2025-03-15 Refactor UI and Fader APIs to improve error handling and update function signatures
2025-03-15 Refactor flash memory functions to return device_error_t for improved error handling
2025-03-15 Remove CLI prompt print statements and update include path for cli.h
2025-03-15 Refactor device handling and error management; add MIDI support and improve CLI initialization
2025-03-15 Code moved to Firmware folder
2025-03-15 .gitignore updated
2025-03-15 Add README files for Documentation, Firmware, and Hardware directories
2025-03-15 Add concept image to README
2025-03-15 Fix image path in README for concept image
2025-03-15 Fix include paths and update CMakeLists for CLI
2025-03-16 Moved midi files to MIDI Apps folder
2025-03-18 Clean code
2025-03-18 Add new hardware files for FaderBay project and KiCad schematics
2025-03-21 Schematic updates
2025-04-27 Kicad project, gerbers and BOM uploaded
2025-04-27 Images uploaded
2025-05-12 Uploaded images to README
2025-05-29 Uploaded schematics
2025-09-25 Uploaded docs from drive
2026-01-18 18/01/26
2026-01-31 31/01/26
2026-05-17 Repo cleanup: update .gitignore, remove clutter, reorganize images
2026-05-17 Add firmware source (STM32F405, NanoLog submodule)
2026-05-17 Update hardware: KiCad, Gerbers, BOM, new schematic variants
2026-05-17 Add Gemini image, remove root BOM/CSV/scripts
2026-05-17 Remove root Faderbay_BOM.pdf
2026-05-19 Implement firmware resource managers, drivers and scheduler integration
2026-05-19 Add clangd config and build script, remove vscode settings
2026-05-19 Add u8g2 submodule and integrate into build
2026-05-19 Implement fader driver with MUX channel scanning
2026-05-19 Add display driver API declarations
2026-05-19 Add Linux build script and fix u8g2 source list
2026-05-19 Remove cv_control module
2026-05-19 Add section comment structure to source files
2026-05-23 Implement application modules, config and device init
2026-05-23 Add NanoLog instrumentation and bug fixes to drivers and resource managers
2026-05-23 Wire NanoLog UART backend via submodule update
2026-05-23 Add pack-sources.ps1 to zip project sources and headers
2026-05-23 Update KiCad project view settings
2026-05-29 Add .gitattributes, extract syscalls stub, tighten build flags
2026-05-29 Expand KiCad .gitignore, untrack generated files, update schematic date
2026-05-29 Fix .gitignore to cover KiCad *-bak files
2026-05-29 Refactor fader subsystem: ADC DMA event-driven, IIR filter, MUX settling
2026-05-29 Refactor button driver: state machine, event queue, long-press and double-click
2026-05-29 Improve encoder driver: detent normalisation, jitter absorption, velocity acceleration
2026-05-29 PCB update
2026-05-29 Update NanoLog submodule to current HEAD
2026-05-29 Remove ST vendor libraries from tracking, add gitignore and gitattributes
    HAL, CMSIS and USB Middleware are regenerated by STM32CubeIDE and do not
    belong in version control. Add .gitattributes to normalise line endings to LF.
2026-05-29 Enable DMA for ADC1 and SPI1, switch SPI transmit to DMA
    CubeMX regeneration adding DMA2 init (streams 0 and 3), IRQ handlers, and
    linking DMA handles to ADC1 and SPI1. ADC sampling extended to 480 cycles for
    MUX settling. SPI prescaler set to /128 for display stability. SPI_SendBuffer
    switched to HAL_SPI_Transmit_DMA with busy-wait polling.
2026-05-29 Fix display driver CS polarity and add init delay, test pattern
    CS was driven inverted (0=high, 1=low). Add 100ms delay before u8g2 init to
    allow display power-on settling. Add DisplayDriver_TestPattern() for hardware
    bringup debugging.
2026-05-29 Fader driver: replace DWT cycle counter settle delay with NOP loop
2026-05-29 Remove old exported hardware files from repo root
    BOM, position file and schematic exports are now managed through KiCad.
2026-05-29 Wrap verbose debug logs in compile-time guards
    FADER_CTRL_DEBUG and MIDI_CTRL_DEBUG flags disable noisy per-sample logging
    in production builds.
2026-05-31 Add UART5 TX DMA; switch button GPIOs from EXTI to polled input
2026-05-31 Button driver: fix active-low polarity, add boot warmup guard; raise ADC cap
2026-05-31 Fader driver: prime IIR filter on boot to suppress spurious MIDI
2026-05-31 Display driver: remove test pattern scaffolding
2026-05-31 Enable FADER_CTRL_DEBUG; demote UI state-change logs to LOGD
2026-05-31 Add flash.sh and pack-sources.sh scripts
2026-06-02 UART: add non-blocking DMA TX ring buffer
2026-06-02 MIDI driver: switch TX to DMA ring
2026-06-02 Fader control: add peek/ack API; midi_control: retry on ring full
2026-06-02 Update NanoLog submodule
2026-06-02 Add Midi tools
2026-06-11 Project backup
2026-06-23 Normalize line endings to LF; clean up ignored files
